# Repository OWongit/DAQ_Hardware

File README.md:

# High-Precision Raspberry Pi DAQ Board

A custom Data Acquisition (DAQ) hat designed for the Raspberry Pi. This board interfaces with industrial sensors (RTDs, Load Cells, Pressure Transducers) to log and display live data with high precision.

The system features a robust, low-noise power architecture that manages 24VDC input to power the sensors, the precision analog circuitry, and the Raspberry Pi itself. It utilizes dual 24-bit ADCs communicating over SPI for high-resolution signal digitization.

## ⚡ Features

* **Multi-Sensor Interface:** Three 15-position D-sub connectors for attaching RTDs, Load Cells, and Pressure Transducers.
* **Input Protection:** Every signal line is protected by TVS diode arrays to guard against ESD and surge events.
* **High-Resolution Sampling:** Dual 24-bit ADCs transmit data via SPI to the Raspberry Pi.
* **Low-Noise Power Architecture:**
    * Accepts 24 VDC input.
    * On-board Buck converters for high-efficiency voltage step-down.
    * LDOs and precision voltage references ensure clean power rails for the ADCs and sensors.
    * High-current supply dedicated to the Raspberry Pi.
* **Compact Design:** PCB fits within a 10cm x 10cm footprint to minimize manufacturing costs.

### 3D Rendering

### Layout View

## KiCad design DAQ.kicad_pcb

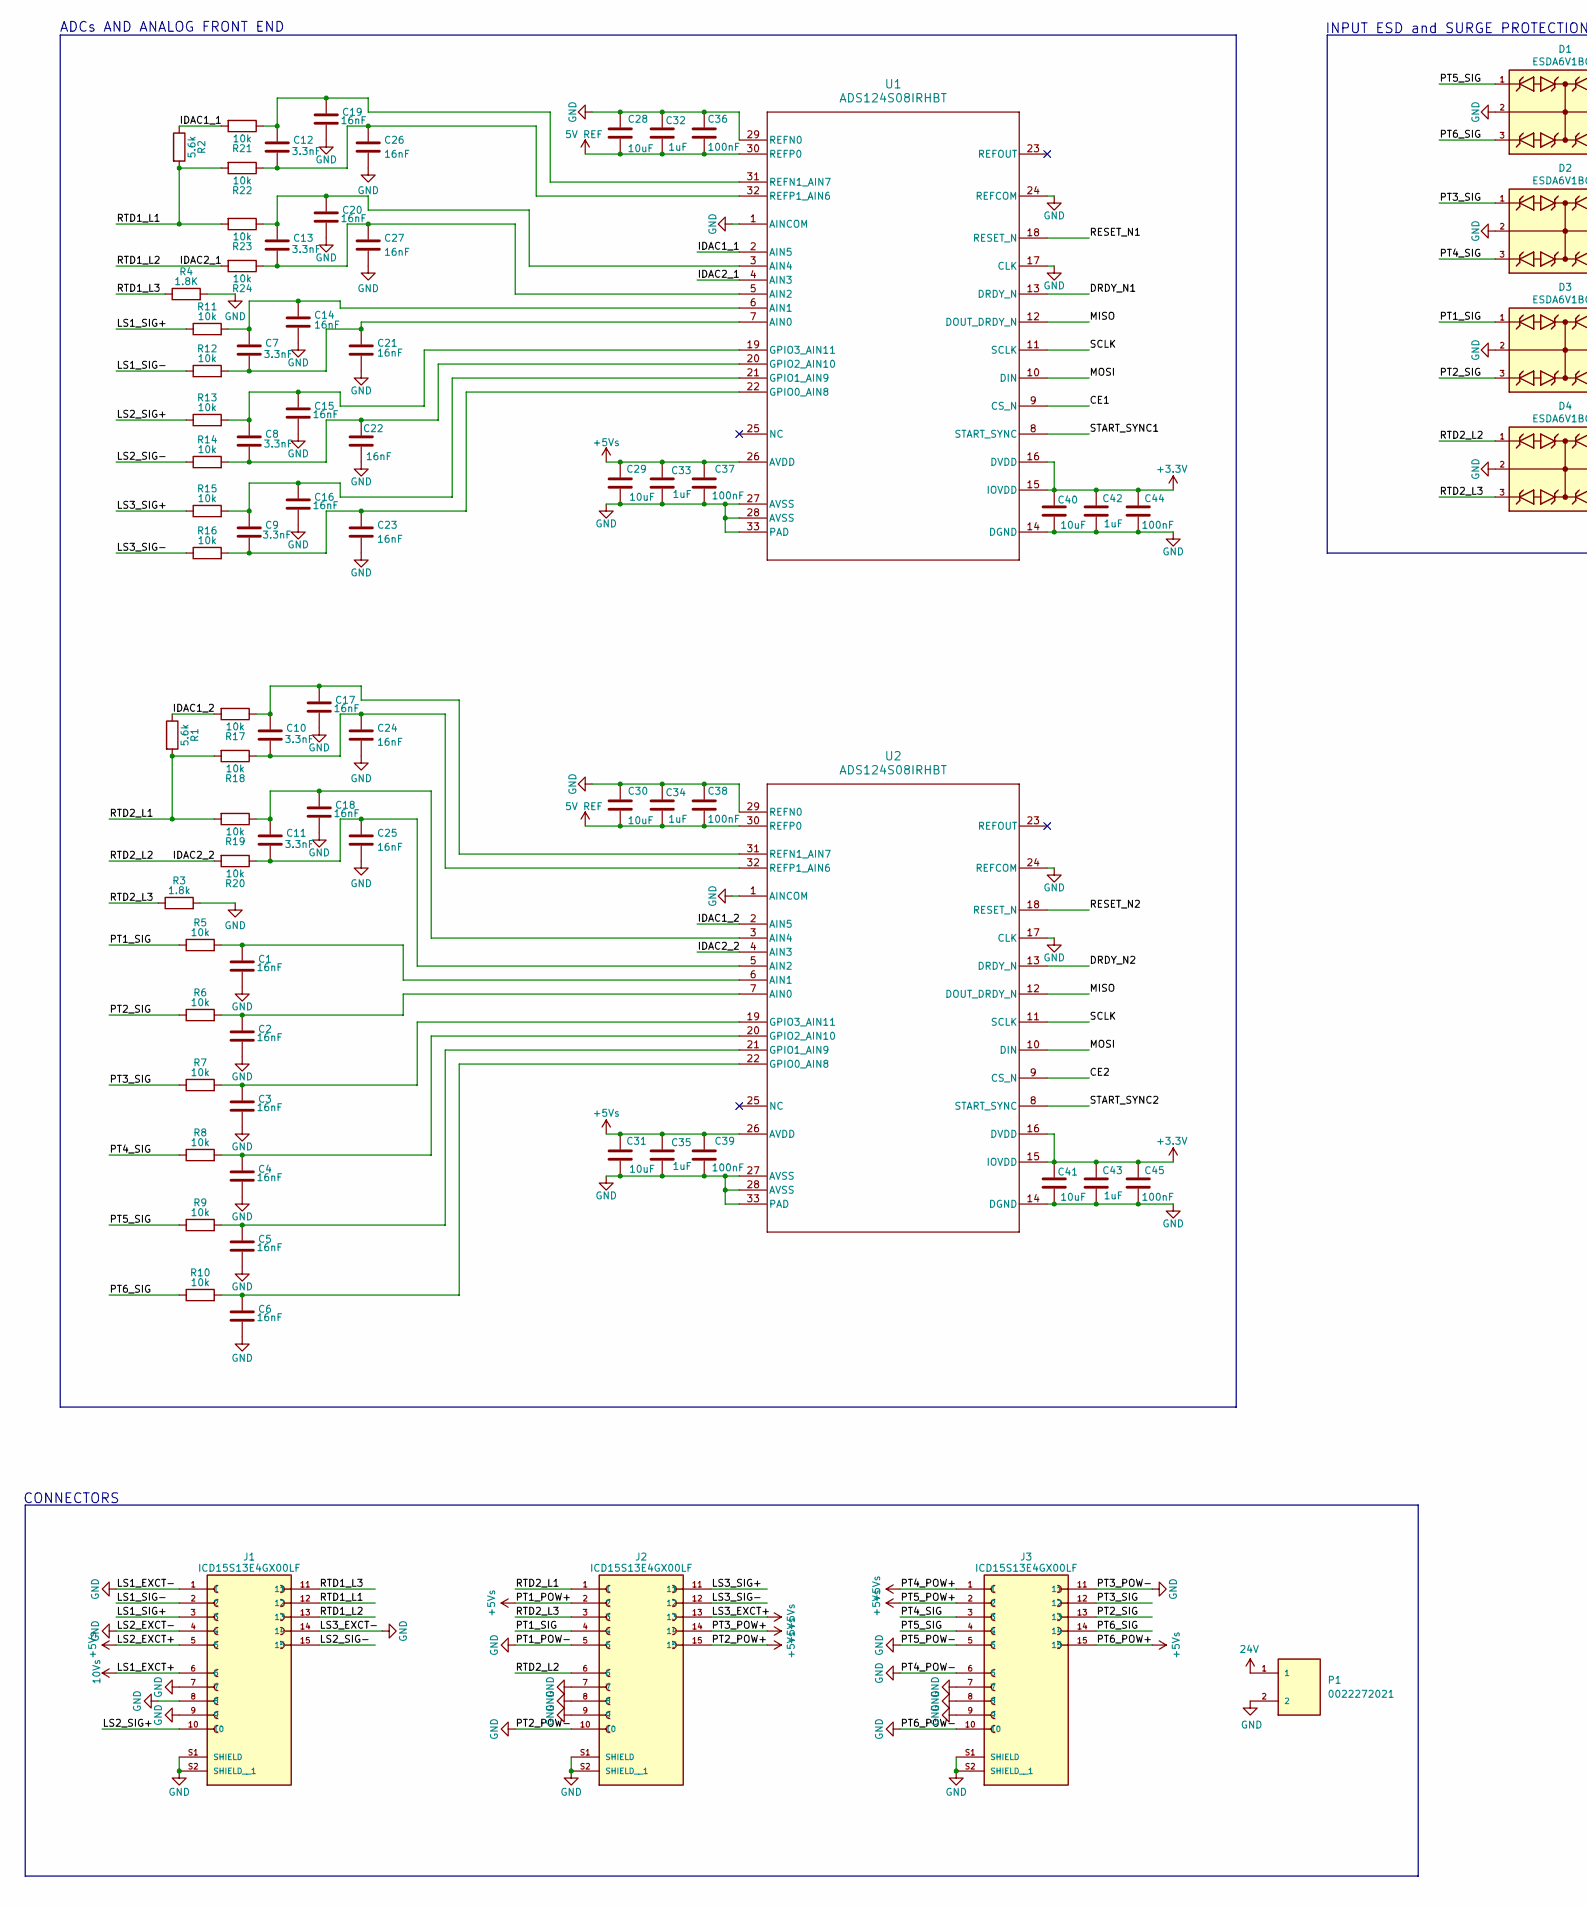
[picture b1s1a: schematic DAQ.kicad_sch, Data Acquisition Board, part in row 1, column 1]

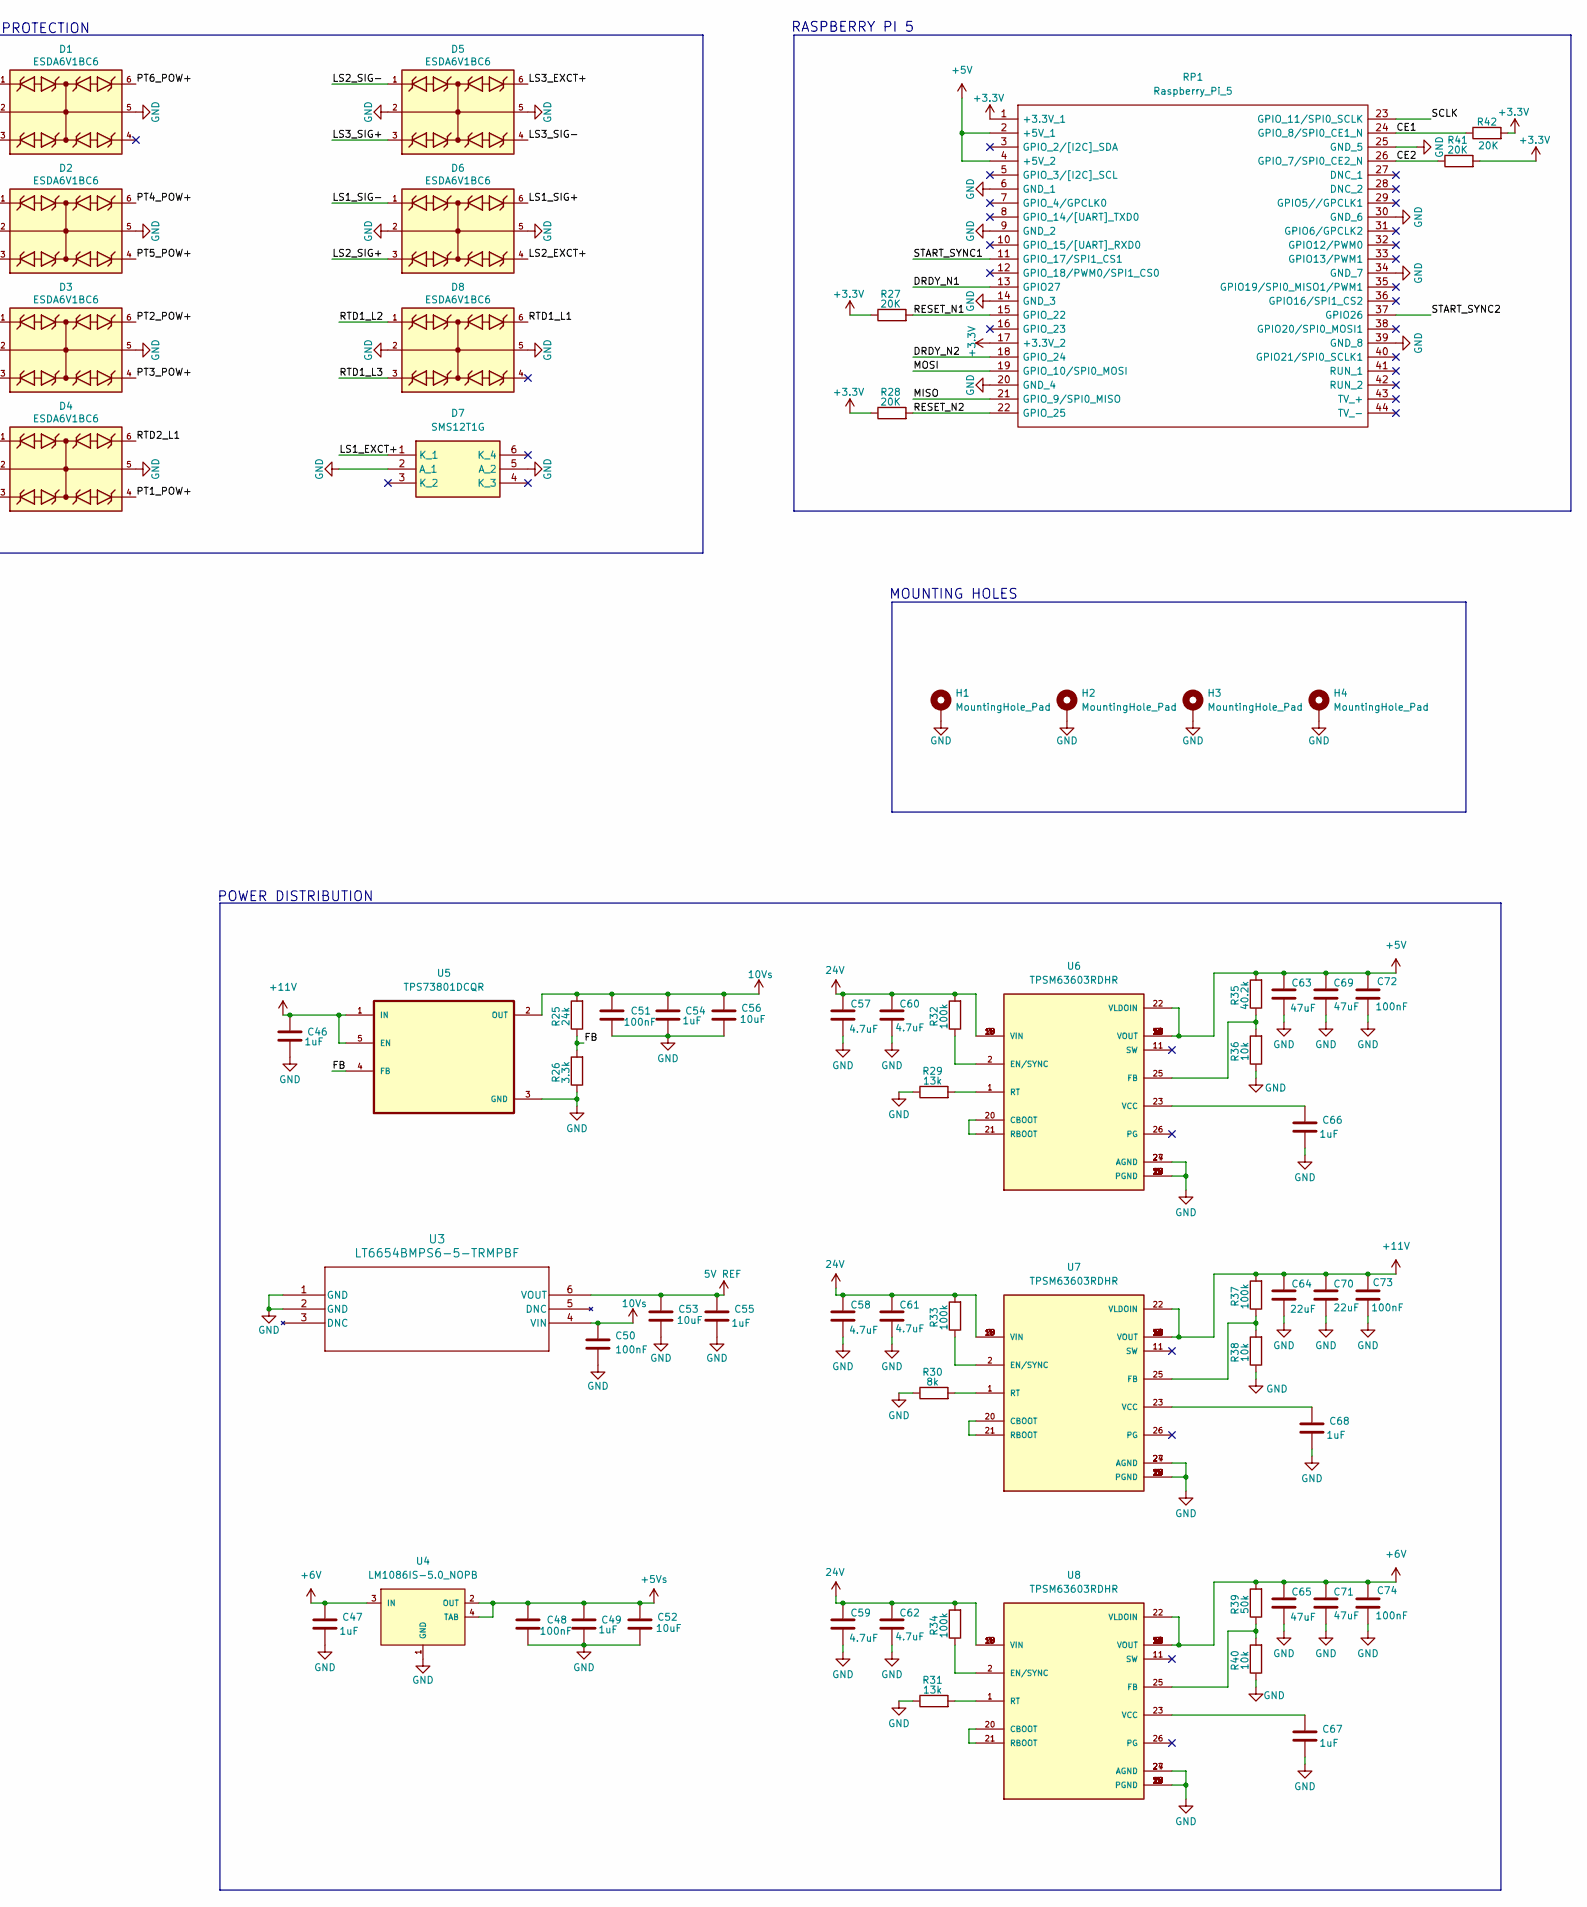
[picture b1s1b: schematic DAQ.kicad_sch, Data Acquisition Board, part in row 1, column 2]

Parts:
C1, C2, C3, C4, C5, C6, C14, C15, C16, C17, C18, C19, C20, C21, C22, C23, C24, C25, C26, C27: 16nF; CAPC3216X95N
C7, C8, C9, C10, C11, C12, C13: 3.3nF; CAP_CL10_SAM
C28, C29, C30, C31, C40, C41, C52, C53, C56: 10uF; CAPC2012X145N
C32, C33, C34, C35, C42, C43, C46, C47, C49, C54, C55, C66, C67, C68: 1uF; CAPC1608X94N
C36, C37, C38, C39, C44, C45, C48, C50, C51, C72, C73, C74: 100nF; CAPC1608X97N
C57, C58, C59, C60, C61, C62: 4.7uF; C_0805_2012Metric_Pad1.18x1.45mm_HandSolder
C63, C65, C69, C71: 47uF; L_1206_3216Metric_Pad1.42x1.75mm_HandSolder
C64, C70: 22uF; L_1206_3216Metric_Pad1.42x1.75mm_HandSolder
D1, D2, D3, D4, D5, D6, D8: ESDA6V1BC6; SOT95P280X145-6N; PARTREV 2
D7: SMS12T1G; SOT95P275X110-6N; Manufacturer_Part_Number SMS12T1G; Mouser Part Number 863-SMS12T1G
H1, H2, H3, H4: MountingHole_Pad; MountingHole_2.5mm_Pad
J1, J2, J3: ICD15S13E4GX00LF; AMPHENOL_ICD15S13E4GX00LF; PARTREV G
P1: 0022272021; MOLEX_0022272021
R1, R2: 5.6k; RC0603N_YAG-M
R3: 1.8k; RC0603N_YAG-M
R4: 1.8K; RC0603N_YAG-M
R5, R6, R7, R8, R9, R10, R11, R12, R13, R14, R15, R16, R17, R18, R19, R20, R21, R22, R23, R24: 10k; RC0603N_YAG-M
R25: 24k; RESC1508X50N
R26: 3.3k; RESC1508X50N
R27, R28, R41, R42: 20K; RESC1508X50N
R29, R31: 13k; RESC1508X50N
R30: 8k; RESC1508X50N
R32, R33, R34, R37: 100k; RESC1508X50N
R35: 40.2k; RESC1508X50N
R36, R38, R40: 10k; RESC1508X50N
R39: 50k; RESC1508X50N
RP1: Raspberry_Pi_5; raspberrypi_2_3; Manufacturer_Part_Number Raspberry Pi 2 or 3
U1, U2: ADS124S08IRHBT; RHB0032M
U3: LT6654BMPS6-5-TRMPBF; TSOT-23_S6_LIT
U4: LM1086IS-5.0_NOPB; TO254P1524X483-4N
U5: TPS73801DCQR; SOT127P706X180-6N
U6, U7, U8: TPSM63603RDHR; CONV_TPSM63602RDHR; PARTREV April 2022

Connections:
5V REF: C28.2, C30.2, C32.2, C34.2, C36.2, C38.2, C53.1, C55.1, U1.30 (REFP0), U2.30 (REFP0), U3.6 (VOUT)
10Vs: C50.1, C51.1, C54.1, C56.1, D7.1 (K_1), J1.6, R25.2, U3.4 (VIN), U5.2 (OUT)
24V: C57.2, C58.2, C59.2, C60.2, C61.2, C62.2, P1.1, R32.2, R33.2, R34.2, U6.3 (VIN), U6.4 (VIN), U6.18 (VIN), U6.19 (VIN), U7.3 (VIN), U7.4 (VIN), U7.18 (VIN), U7.19 (VIN), U8.3 (VIN), U8.4 (VIN), U8.18 (VIN), U8.19 (VIN)
+3.3V: C40.1, C41.1, C42.1, C43.1, C44.1, C45.1, R27.1, R28.1, R41.2, R42.2, RP1.1 (+3.3V_1), RP1.17 (+3.3V_2), U1.15 (IOVDD), U1.16 (DVDD), U2.15 (IOVDD), U2.16 (DVDD)
+5V: C63.2, C69.2, C72.1, R35.2, RP1.2 (+5V_1), RP1.4 (+5V_2), U6.7 (VOUT), U6.8 (VOUT), U6.9 (VOUT), U6.10 (VOUT), U6.12 (VOUT), U6.13 (VOUT), U6.14 (VOUT), U6.15 (VOUT), U6.22 (VLDOIN), U6.30 (VOUT), U6.31
+5Vs: C29.1, C31.1, C33.1, C35.1, C37.1, C39.1, C48.1, C49.1, C52.1, D1.6, D2.4, D2.6, D3.4, D3.6, D4.4, D5.6, D6.4, J1.5, J2.2, J2.13, J2.14, J2.15, J3.1, J3.2, J3.15, U1.26 (AVDD), U2.26 (AVDD), U4.2 (OUT), U4.4 (TAB)
+6V: C47.1, C65.2, C71.2, C74.1, R39.2, U4.3 (IN), U8.7 (VOUT), U8.8 (VOUT), U8.9 (VOUT), U8.10 (VOUT), U8.12 (VOUT), U8.13 (VOUT), U8.14 (VOUT), U8.15 (VOUT), U8.22 (VLDOIN), U8.30 (VOUT), U8.31
+11V: C46.1, C64.2, C70.2, C73.1, R37.2, U5.1 (IN), U5.5 (EN), U7.7 (VOUT), U7.8 (VOUT), U7.9 (VOUT), U7.10 (VOUT), U7.12 (VOUT), U7.13 (VOUT), U7.14 (VOUT), U7.15 (VOUT), U7.22 (VLDOIN), U7.30 (VOUT), U7.31
/CE1: R42.1, RP1.24 (GPIO_8/SPI0_CE1_N), U1.9 (CS_N)
/CE2: R41.1, RP1.26 (GPIO_7/SPI0_CE2_N), U2.9 (CS_N)
/DRDY_N1: RP1.13 (GPIO27), U1.13 (DRDY_N)
/DRDY_N2: RP1.18 (GPIO_24), U2.13 (DRDY_N)
/FB: R25.1, R26.2, U5.4 (FB)
/IDAC1_1: R2.1, R21.2, U1.2 (AIN5)
/IDAC1_2: R1.1, R17.2, U2.2 (AIN5)
/IDAC2_1: D8.1, J1.13, R24.2, U1.4 (AIN3)
/IDAC2_2: D4.1, J2.6, R20.2, U2.4 (AIN3)
/LS1_SIG+: D6.6, J1.3, R11.1
/LS1_SIG-: D6.1, J1.2, R12.1
/LS2_SIG+: D6.3, J1.10, R13.1
/LS2_SIG-: D5.1, J1.15, R14.1
/LS3_SIG+: D5.3, J2.11, R15.1
/LS3_SIG-: D5.4, J2.12, R16.1
/MISO: RP1.21 (GPIO_9/SPI0_MISO), U1.12 (DOUT_DRDY_N), U2.12 (DOUT_DRDY_N)
/MOSI: RP1.19 (GPIO_10/SPI0_MOSI), U1.10 (DIN), U2.10 (DIN)
/PT1_SIG: D3.1, J2.4, R5.1
/PT2_SIG: D3.3, J3.13, R6.1
/PT3_SIG: D2.1, J3.12, R7.1
/PT4_SIG: D2.3, J3.3, R8.1
/PT5_SIG: D1.1, J3.4, R9.1
/PT6_SIG: D1.3, J3.14, R10.1
/RESET_N1: R27.2, RP1.15 (GPIO_22), U1.18 (RESET_N)
/RESET_N2: R28.2, RP1.22 (GPIO_25), U2.18 (RESET_N)
/RTD1_L1: D8.6, J1.12, R2.2, R22.2, R23.2
/RTD1_L3: D8.3, J1.11, R4.1
/RTD2_L1: D4.6, J2.1, R1.2, R18.2, R19.2
/RTD2_L3: D4.3, J2.3, R3.1
/SCLK: RP1.23 (GPIO_11/SPI0_SCLK), U1.11 (SCLK), U2.11 (SCLK)
/START_SYNC1: RP1.11 (GPIO_17/SPI1_CS1), U1.8 (START_SYNC)
/START_SYNC2: RP1.37 (GPIO26), U2.8 (START_SYNC)
GND: C1.2, C2.2, C3.2, C4.2, C5.2, C6.2, C14.2, C15.2, C16.2, C17.2, C18.2, C19.2, C20.2, C21.2, C22.2, C23.2, C24.2, C25.2, C26.2, C27.2, C28.1, C29.2, C30.1, C31.2, C32.1, C33.2, C34.1, C35.2, C36.1, C37.2, C38.1, C39.2, C40.2, C41.2, C42.2, C43.2, C44.2, C45.2, C46.2, C47.2, C48.2, C49.2, C50.2, C51.2, C52.2, C53.2, C54.2, C55.2, C56.2, C57.1, C58.1, C59.1, C60.1, C61.1, C62.1, C63.1, C64.1, C65.1, C66.2, C67.2, C68.2, C69.1, C70.1, C71.1, C72.2, C73.2, C74.2, D1.2, D1.5, D2.2, D2.5, D3.2, D3.5, D4.2, D4.5, D5.2, D5.5, D6.2, D6.5, D7.2 (A_1), D7.5 (A_2), D8.2, D8.5, H1.1, H2.1, H3.1, H4.1, J1.1, J1.4, J1.7, J1.8, J1.9, J1.14, J1.S1 (SHIELD), J1.S2 (SHIELD__1), J2.5, J2.7, J2.8, J2.9, J2.10, J2.S1 (SHIELD), J2.S2 (SHIELD__1), J3.5, J3.6, J3.7, J3.8, J3.9, J3.10, J3.11, J3.S1 (SHIELD), J3.S2 (SHIELD__1), P1.2, R3.2, R4.2, R26.1, R29.1, R30.1, R31.1, R36.1, R38.1, R40.1, RP1.6 (GND_1), RP1.9 (GND_2), RP1.14 (GND_3), RP1.20 (GND_4), RP1.25 (GND_5), RP1.30 (GND_6), RP1.34 (GND_7), RP1.39 (GND_8), U1.1 (AINCOM), U1.14 (DGND), U1.17 (CLK), U1.24 (REFCOM), U1.27 (AVSS), U1.28 (AVSS), U1.29 (REFN0), U1.33 (PAD), U1.V, U2.1 (AINCOM), U2.14 (DGND), U2.17 (CLK), U2.24 (REFCOM), U2.27 (AVSS), U2.28 (AVSS), U2.29 (REFN0), U2.33 (PAD), U2.V, U3.1 (GND), U3.2 (GND), U4.1 (GND), U5.3 (GND), U6.5 (PGND), U6.6 (PGND), U6.16 (PGND), U6.17 (PGND), U6.24 (AGND), U6.27 (AGND), U6.28 (PGND), U6.29 (PGND), U6.32, U6.33, U6.34, U6.35, U6.36, U7.5 (PGND), U7.6 (PGND), U7.16 (PGND), U7.17 (PGND), U7.24 (AGND), U7.27 (AGND), U7.28 (PGND), U7.29 (PGND), U7.32, U7.33, U7.34, U7.35, U7.36, U8.5 (PGND), U8.6 (PGND), U8.16 (PGND), U8.17 (PGND), U8.24 (AGND), U8.27 (AGND), U8.28 (PGND), U8.29 (PGND), U8.32, U8.33, U8.34, U8.35, U8.36
unnamed: C7.2, C21.1, R12.2, U1.7 (AIN0)
unnamed: C7.1, C14.1, R11.2, U1.6 (AIN1)
unnamed: C13.2, C27.1, R24.1, U1.5 (AIN2)
unnamed: C13.1, C20.1, R23.1, U1.3 (AIN4)
unnamed: C9.2, C23.1, R16.2, U1.22 (GPIO0_AIN8)
unnamed: C9.1, C16.1, R15.2, U1.21 (GPIO1_AIN9)
unnamed: C8.2, C22.1, R14.2, U1.20 (GPIO2_AIN10)
unnamed: C8.1, C15.1, R13.2, U1.19 (GPIO3_AIN11)
unnamed: C12.1, C19.1, R21.1, U1.31 (REFN1_AIN7)
unnamed: C12.2, C26.1, R22.1, U1.32 (REFP1_AIN6)
unnamed: C2.1, R6.2, U2.7 (AIN0)
unnamed: C1.1, R5.2, U2.6 (AIN1)
unnamed: C11.2, C25.1, R20.1, U2.5 (AIN2)
unnamed: C11.1, C18.1, R19.1, U2.3 (AIN4)
unnamed: C6.1, R10.2, U2.22 (GPIO0_AIN8)
unnamed: C5.1, R9.2, U2.21 (GPIO1_AIN9)
unnamed: C4.1, R8.2, U2.20 (GPIO2_AIN10)
unnamed: C3.1, R7.2, U2.19 (GPIO3_AIN11)
unnamed: C10.1, C17.1, R17.1, U2.31 (REFN1_AIN7)
unnamed: C10.2, C24.1, R18.1, U2.32 (REFP1_AIN6)
unnamed: U6.20 (CBOOT), U6.21 (RBOOT)
unnamed: R32.1, U6.2 (EN/SYNC)
unnamed: R35.1, R36.2, U6.25 (FB)
unnamed: R29.2, U6.1 (RT)
unnamed: C66.1, U6.23 (VCC)
unnamed: U7.20 (CBOOT), U7.21 (RBOOT)
unnamed: R33.1, U7.2 (EN/SYNC)
unnamed: R37.1, R38.2, U7.25 (FB)
unnamed: R30.2, U7.1 (RT)
unnamed: C68.1, U7.23 (VCC)
unnamed: U8.20 (CBOOT), U8.21 (RBOOT)
unnamed: R34.1, U8.2 (EN/SYNC)
unnamed: R39.1, R40.2, U8.25 (FB)
unnamed: R31.2, U8.1 (RT)
unnamed: C67.1, U8.23 (VCC)

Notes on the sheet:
RASPBERRY PI 5
MOUNTING HOLES
INPUT ESD and SURGE PROTECTION
POWER DISTRIBUTION
ADCs AND ANALOG FRONT END
CONNECTORS

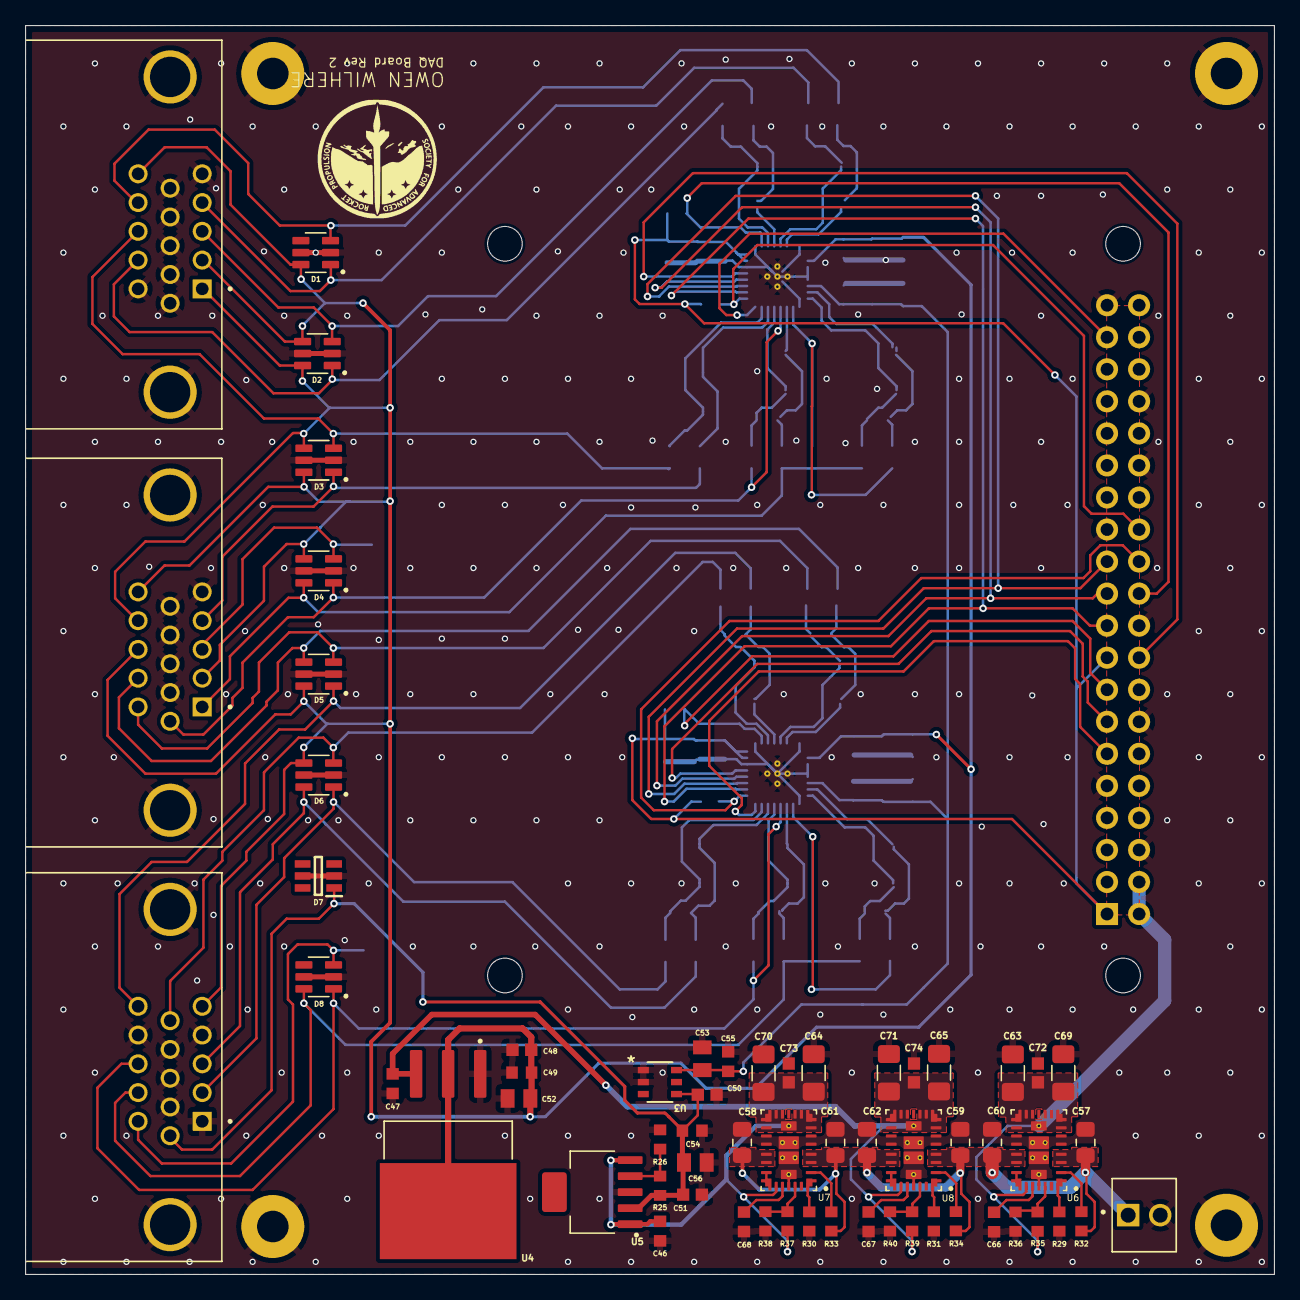
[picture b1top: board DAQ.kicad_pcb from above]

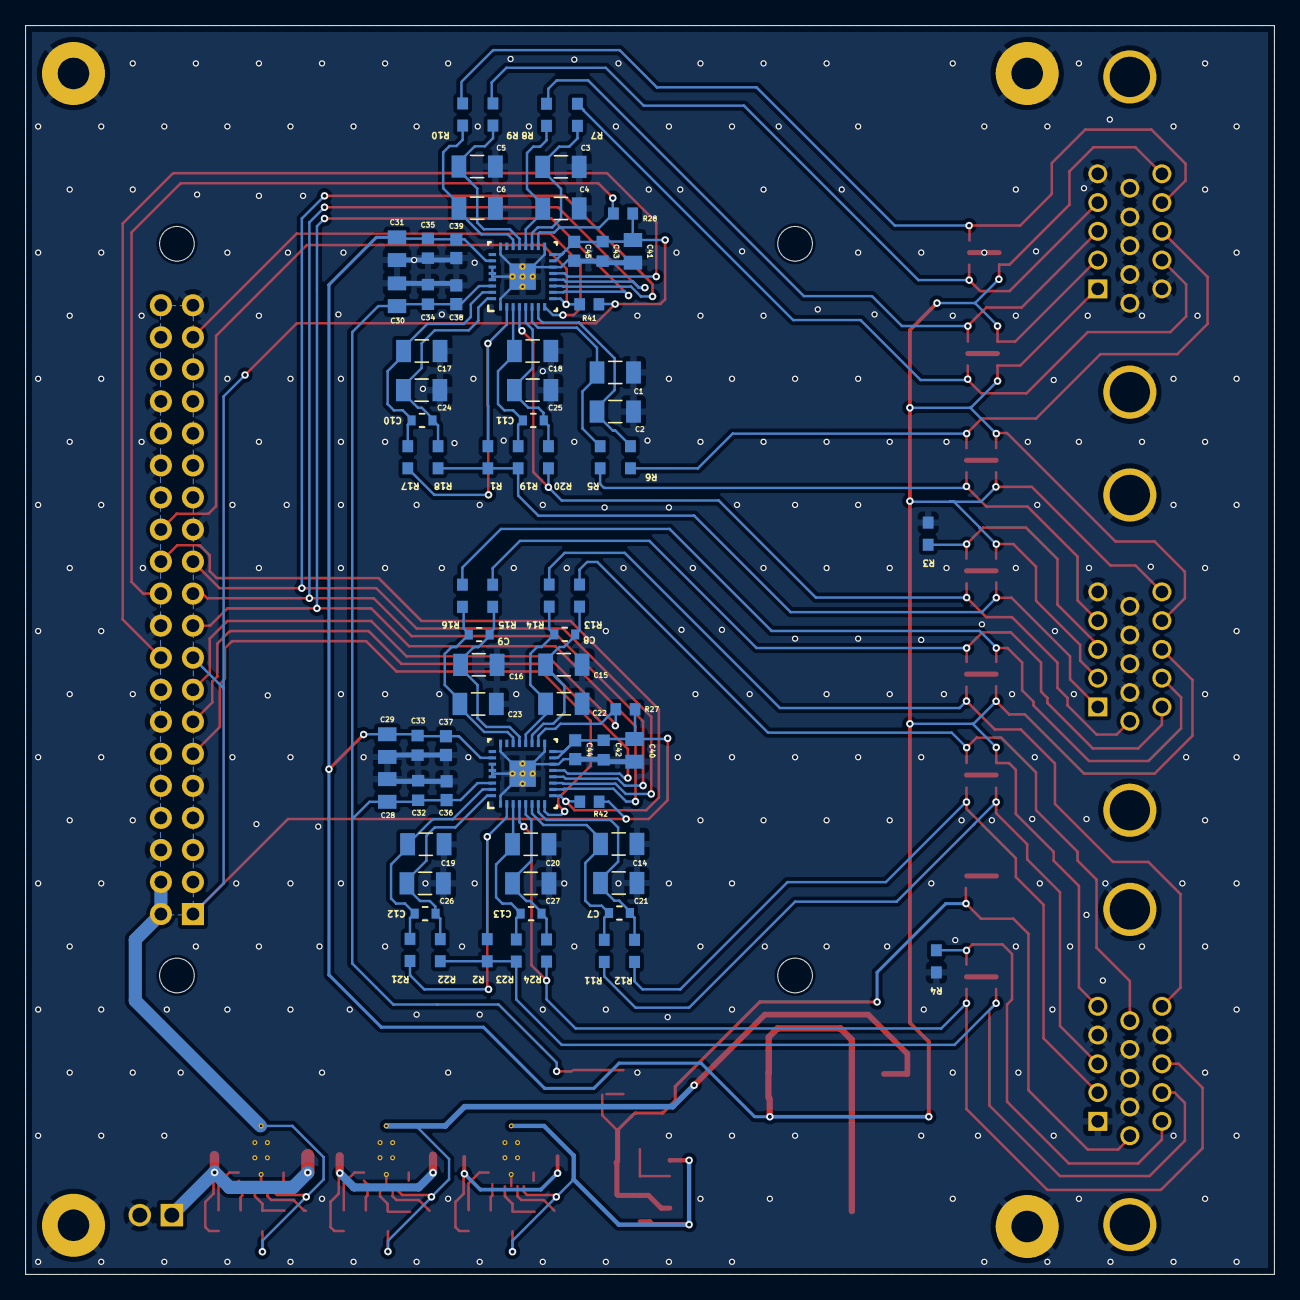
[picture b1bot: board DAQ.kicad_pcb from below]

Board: 2 copper layers, 99.0 x 99.0 mm, 141 parts (76 on the bottom side), 76 nets.

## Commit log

2026-01-15 Added Files
2026-04-15 Clean up schematic
2026-04-16 Added differential amplifiers
